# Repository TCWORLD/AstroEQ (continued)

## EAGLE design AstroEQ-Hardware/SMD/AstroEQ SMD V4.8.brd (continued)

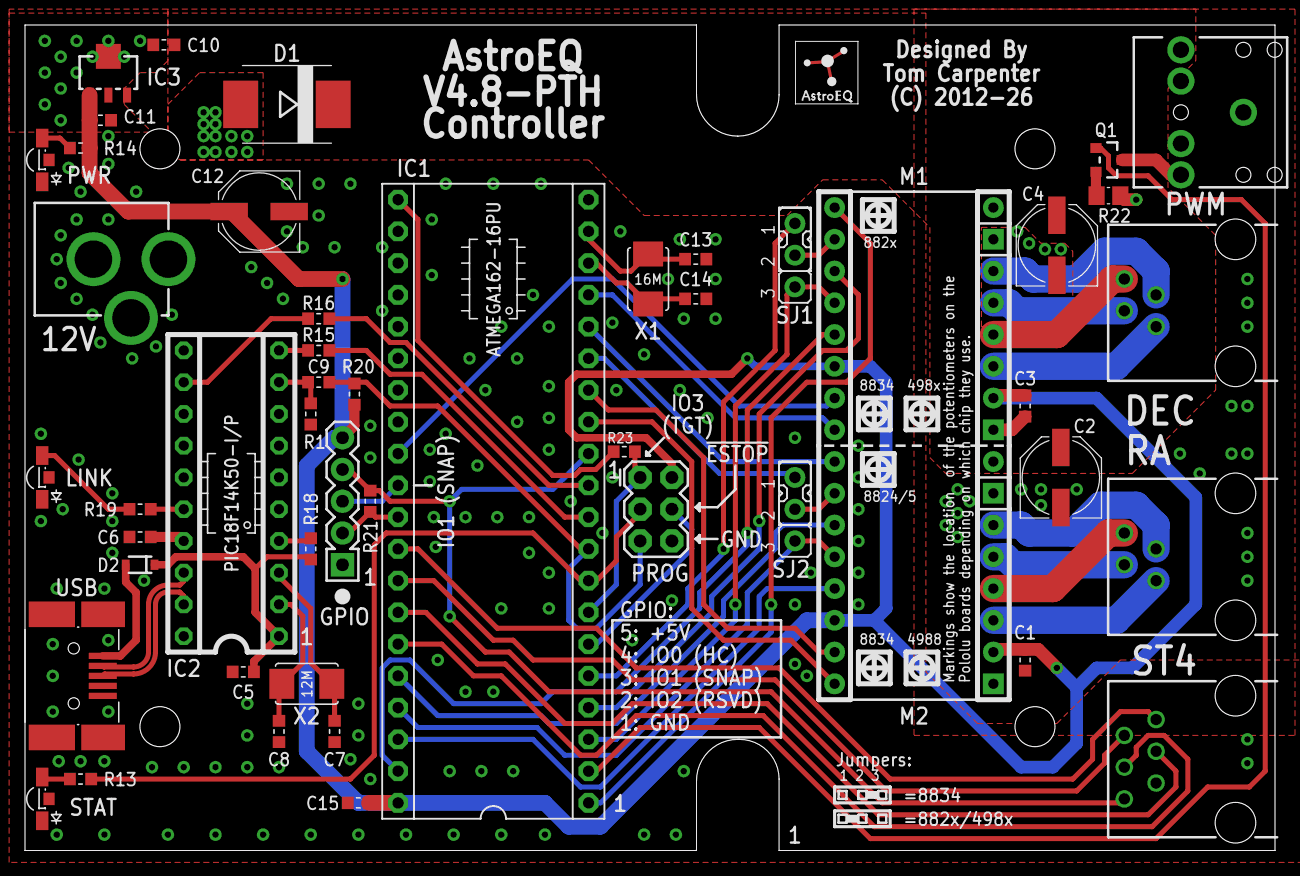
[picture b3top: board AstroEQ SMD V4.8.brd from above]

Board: 2 copper layers, 100.0 x 66.0 mm, 55 parts (0 on the bottom side), 62 nets.

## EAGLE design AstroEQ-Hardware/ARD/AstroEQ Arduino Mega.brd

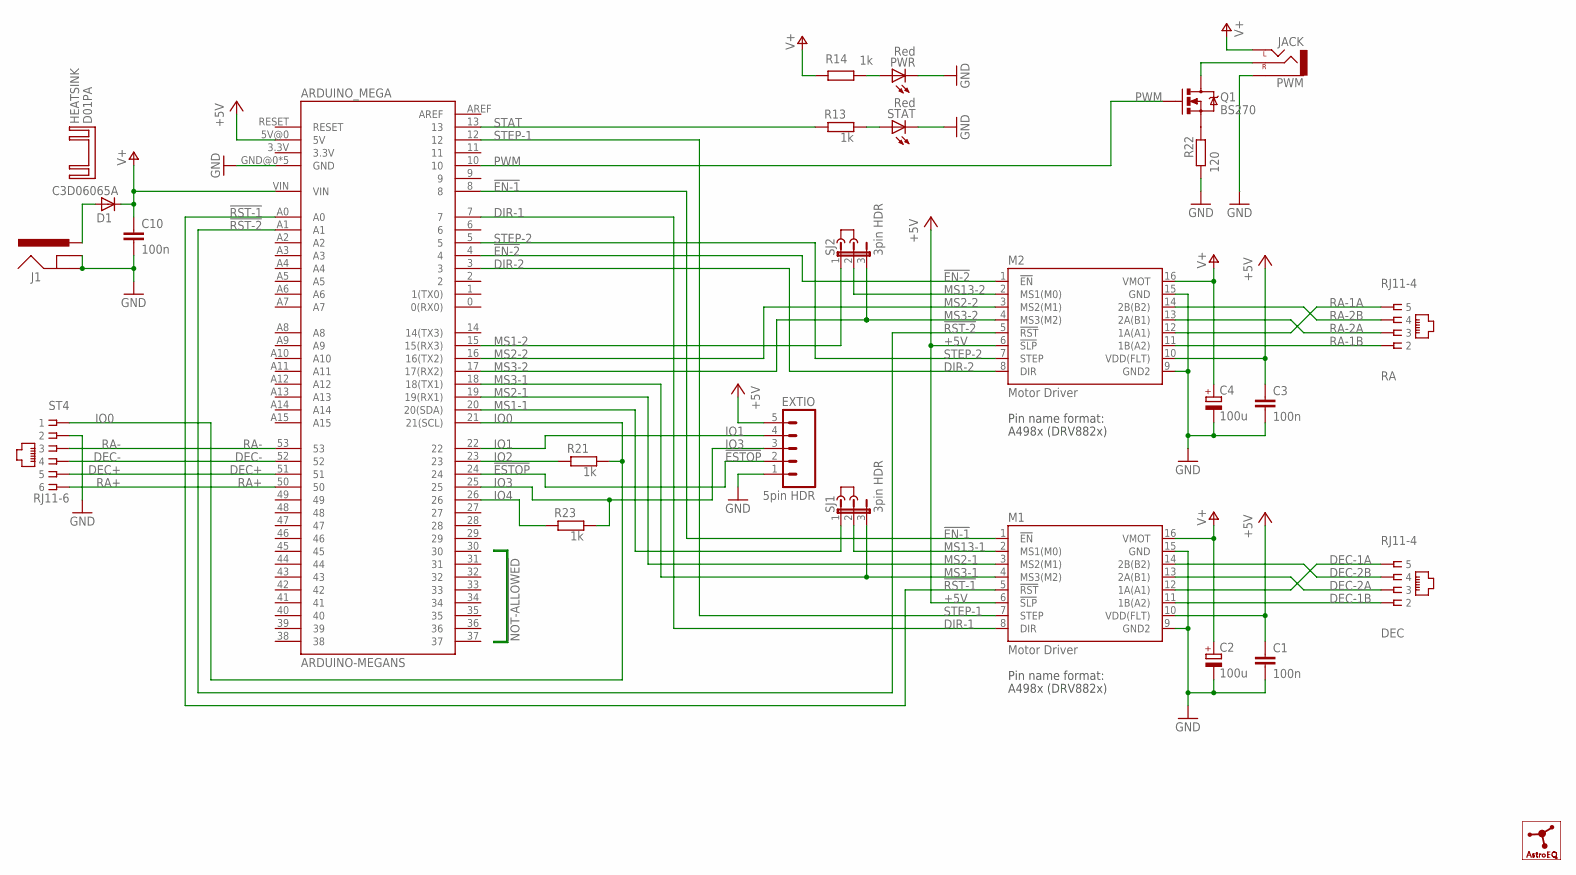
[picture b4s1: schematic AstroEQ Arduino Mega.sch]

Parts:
ARDUINO_MEGA: ARDUINO-MEGANS; ARDUINO_MEGA_NS
C1, C3, C10: 100n; C025-024X044; MPN SR205C104KAR
C2, C4: 100u; E2,5-7; MPN MCGPR25V107M6.3X11
D1: C3D06065A; TO220ACS; MPN C3D06065A
DEC: RJ11-4; RJ11-NO_SHIELD-4; MPN 95501-2641
EXTIO: 5pin HDR; 1X05
HEATSINK: D01PA
J1: POWER_JACKPTH; POWER_JACK_PTH; MPN MJ-179PH
J2, J3: DNI; JUMP; MPN 969102-0000-DA
LOGO1: ASTROEQ8MM; ASTROEQ
M1, M2: Motor Driver; DIP16-W; MPN CES-116-01-T-S
PWM: JACK; AUDIO-JACK-3.5MM-VERT
PWR: Red; LED3MM; MPN L-424HDT
Q1: BS270; TO-92; MPN BS270
R13: 1k; 0204/5; MPN MF12 1K
R14, R21, R23: 1k; 0204/7; MPN MF12 1K
R22: 120; 0204/7; MPN MF12 120R
RA: RJ11-4; RJ11-NO_SHIELD-4; MPN 95501-2641
SJ1, SJ2: 3pin HDR; JP2; MPN M20-9990345.
ST4: RJ11-6; RJ11-NO_SHIELD
STAT: Red; LED3MM; MPN L-424HDT

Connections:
!EN-1: ARDUINO_MEGA.8, M1.1 (!EN)
!EN-2: ARDUINO_MEGA.4, M2.1 (!EN)
!ESTOP: ARDUINO_MEGA.24, EXTIO.2
!RST-1: ARDUINO_MEGA.A0, M1.5 (!RST)
!RST-2: ARDUINO_MEGA.A1, M2.5 (!RST)
+5V: ARDUINO_MEGA.5V@0 (5V), C1.1, C3.1, EXTIO.5, M1.6 (!SLP), M1.10 (VDD(FLT)), M2.6 (!SLP), M2.10 (VDD(FLT))
DEC+: ARDUINO_MEGA.51, ST4.5
DEC-: ARDUINO_MEGA.52, ST4.4
DEC-1A: DEC.5, M1.12 (1A(A1))
DEC-1B: DEC.2, M1.11 (1B(A2))
DEC-2A: DEC.3, M1.13 (2A(B1))
DEC-2B: DEC.4, M1.14 (2B(B2))
DIR-1: ARDUINO_MEGA.7, M1.8 (DIR)
DIR-2: ARDUINO_MEGA.3, M2.8 (DIR)
GND: ARDUINO_MEGA.GND@0 (GND), ARDUINO_MEGA.GND@1 (GND), ARDUINO_MEGA.GND@2 (GND), ARDUINO_MEGA.GND@3 (GND), ARDUINO_MEGA.GND@4 (GND), C1.2, C2.-, C3.2, C4.-, C10.2, EXTIO.1, J1.GND, J1.GNDBREAK, M1.9 (GND2), M1.15 (GND), M2.9 (GND2), M2.15 (GND), PWM.1 (SLEEVE), PWR.K (C), R22.1, ST4.2, STAT.K (C)
IO0: ARDUINO_MEGA.21 (21(SCL)), R21.2, ST4.1
IO1: ARDUINO_MEGA.22, EXTIO.4
IO2: ARDUINO_MEGA.23, R21.1
IO3: ARDUINO_MEGA.25, EXTIO.3, R23.2
IO4: ARDUINO_MEGA.26, R23.1
MS1-1: ARDUINO_MEGA.20 (20(SDA)), SJ1.1
MS1-2: ARDUINO_MEGA.15 (15(RX3)), SJ2.1
MS2-1: ARDUINO_MEGA.19 (19(RX1)), M1.3 (MS2(M1))
MS2-2: ARDUINO_MEGA.16 (16(TX2)), M2.3 (MS2(M1))
MS3-1: ARDUINO_MEGA.18 (18(TX1)), M1.4 (MS3(M2)), SJ1.3
MS3-2: ARDUINO_MEGA.17 (17(RX2)), M2.4 (MS3(M2)), SJ2.3
MS13-1: M1.2 (MS1(M0)), SJ1.2
MS13-2: M2.2 (MS1(M0)), SJ2.2
PWM: ARDUINO_MEGA.10, Q1.2 (G)
PWM-ILIM: Q1.3 (S), R22.2
PWM-OUT: PWM.3 (RIGHT), Q1.1 (D)
PWRLED: PWR.A, R14.2
RA+: ARDUINO_MEGA.50, ST4.6
RA-: ARDUINO_MEGA.53, ST4.3
RA-1A: M2.12 (1A(A1)), RA.5
RA-1B: M2.11 (1B(A2)), RA.2
RA-2A: M2.13 (2A(B1)), RA.3
RA-2B: M2.14 (2B(B2)), RA.4
STAT: ARDUINO_MEGA.13, R13.1
STATLED: R13.2, STAT.A
STEP-1: ARDUINO_MEGA.12, M1.7 (STEP)
STEP-2: ARDUINO_MEGA.5, M2.7 (STEP)
V+: ARDUINO_MEGA.VIN, C2.+, C4.+, C10.1, D1.C, M1.16 (VMOT), M2.16 (VMOT), PWM.2 (LEFT), R14.1
VIN: D1.A, J1.PWR

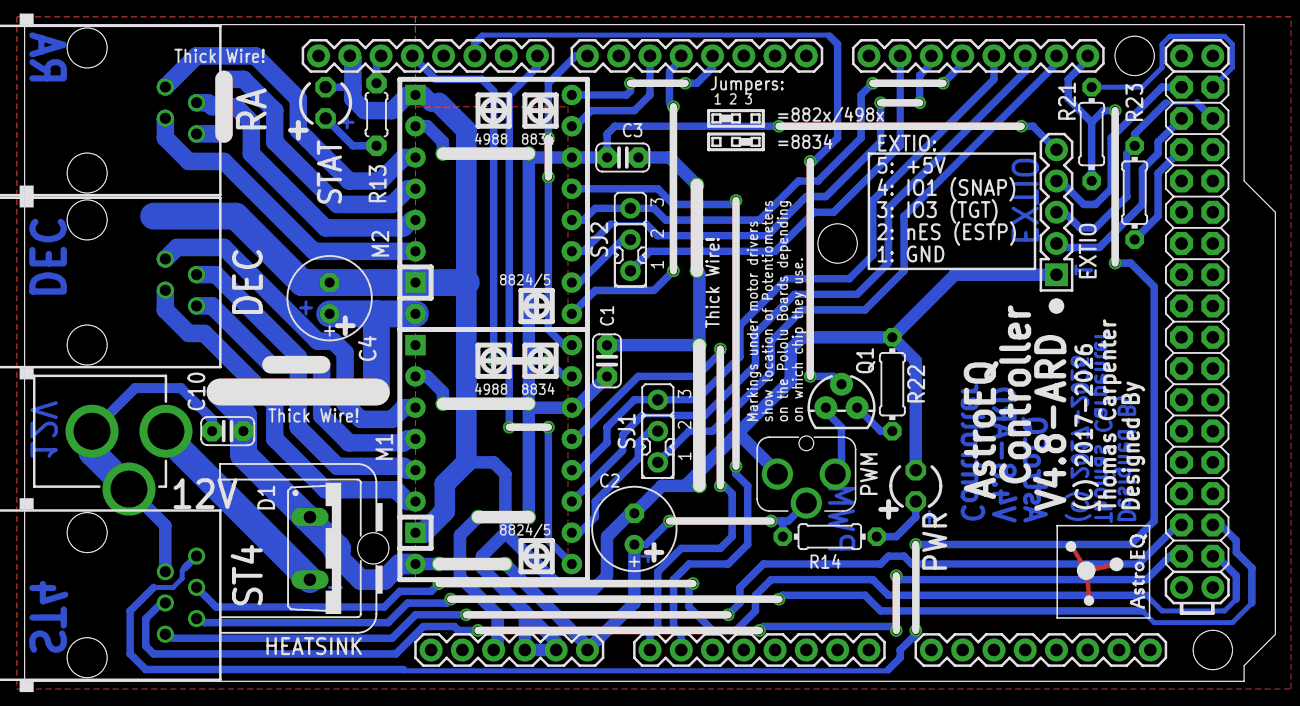
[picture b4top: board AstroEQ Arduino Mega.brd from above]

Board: 2 copper layers, 101.6 x 53.3 mm, 29 parts (0 on the bottom side), 44 nets.

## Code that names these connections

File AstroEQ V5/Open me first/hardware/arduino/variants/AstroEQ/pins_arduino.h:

/*
  pins_arduino.h - Pin definition functions for Arduino
  Part of Arduino - http://www.arduino.cc/

  Copyright (c) 2007 David A. Mellis

  This library is free software; you can redistribute it and/or
  modify it under the terms of the GNU Lesser General Public
  License as published by the Free Software Foundation; either
  version 2.1 of the License, or (at your option) any later version.

  This library is distributed in the hope that it will be useful,
  but WITHOUT ANY WARRANTY; without even the implied warranty of
  MERCHANTABILITY or FITNESS FOR A PARTICULAR PURPOSE.  See the GNU
  Lesser General Public License for more details.

  You should have received a copy of the GNU Lesser General
  Public License along with this library; if not, write to the
  Free Software Foundation, Inc., 59 Temple Place, Suite 330,
  Boston, MA  02111-1307  USA

  $Id: wiring.h 249 2007-02-03 16:52:51Z mellis $
*/

#ifndef Pins_Arduino_h
#define Pins_Arduino_h

#include <avr/pgmspace.h>

#define NUM_DIGITAL_PINS            35
#define NUM_ANALOG_INPUTS           0
#define analogInputToDigitalPin(p)  (-1)

#define digitalPinHasPWM(p)         ((p) == 5 || (p) == 6 || (p) == 8 || (p) == 9 || (p) == 10 || (p) == 30)

const static uint8_t SS   = 10;
const static uint8_t MOSI = 11;
const static uint8_t MISO = 12;
const static uint8_t SCK  = 13;

const static uint8_t LED_BUILTIN = 13;

#define digitalPinToPCICR(p)    ( (((p) >= 14) && ((p) <= 17)) || \
                                  (((p) >= 20) && ((p) <= 27)) || \
                                  (((p) >= 31) && ((p) <= 34)) ? (&PCICR) : ((uint8_t *)0) )
								  
#define digitalPinToPCICRbit(p) ( (((p) >= 20) && ((p) <= 27)) ? 0 : 1 )

#define digitalPinToPCMSK(p)    ( (((p) >= 20) && ((p) <= 27)) ? (&PCMSK0) : \
								  (((p) >= 14) && ((p) <= 17)) || \
                                  (((p) >= 31) && ((p) <= 34)) ? (&PCMSK1) : ((uint8_t *)0) )

#define digitalPinToPCMSKbit(p) ( (((p) >= 20) && ((p) <= 27)) ? ((p) - 20) : \
								  (((p) >= 14) && ((p) <= 17)) ? ((p) - 14) : ((p) - 27) )

#ifdef ARDUINO_MAIN

// On the Arduino board, digital pins are also used
// for the analog output (software PWM).

// ATMEL ATMEGA162 / ARDUINO
//
//                  +-\/-+
//  PWM(0)  (D 8) PB0  1|    |40  VCC
//  PWM(2)  (D 9) PB1  2|    |39  PA0 (D14)
//          (D19) PB2  3|    |38  PA1 (D15)
//          (D18) PB3  4|    |37  PA2 (D16)
// PWM(3B)  (D10) PB4  5|    |36  PA3 (D17)
//          (D11) PB5  6|    |35  PA4 (D31)
//          (D12) PB6  7|    |34  PA5 (D32)
//          (D13) PB7  8|    |33  PA6 (D33)
//                RST  9|    |32  PA7 (D34)
//          (D 0) PD0 10|    |31  PE0 (D28)
//          (D 1) PD1 11|    |30  PE1 (D29)
//          (D 2) PD2 12|    |29  PE2 (D30) PWM(1B)
//          (D 3) PD3 13|    |28  PC7 (D27)
// PWM(3A)  (D 5) PD4 14|    |27  PC6 (D26)
// PWM(1A)  (D 6) PD5 15|    |26  PC5 (D25)
//          (D 4) PD6 16|    |25  PC4 (D24)
//          (D 7) PD7 17|    |24  PC3 (D23)
//                XT2 18|    |23  PC2 (D22)
//                XT1 19|    |22  PC1 (D21)
//                GND 20|    |21  PC0 (D20)
//                      +----+
//


// these arrays map port names (e.g. port B) to the
// appropriate addresses for various functions (e.g. reading
// and writing)
const uint16_t PROGMEM port_to_mode_PGM[] = {
	NOT_A_PORT,
	(uint16_t) &DDRA,
	(uint16_t) &DDRB,
	(uint16_t) &DDRC,
	(uint16_t) &DDRD,
	(uint16_t) &DDRE,
};

const uint16_t PROGMEM port_to_output_PGM[] = {
	NOT_A_PORT,
	(uint16_t) &PORTA,
	(uint16_t) &PORTB,
	(uint16_t) &PORTC,
	(uint16_t) &PORTD,
	(uint16_t) &PORTE,
};

const uint16_t PROGMEM port_to_input_PGM[] = {
	NOT_A_PORT,
	(uint16_t) &PINA,
	(uint16_t) &PINB,
	(uint16_t) &PINC,
	(uint16_t) &PIND,
	(uint16_t) &PINE,
};

const uint8_t PROGMEM digital_pin_to_port_PGM[] = {
	PD, /* 0 */
	PD,
	PD,
	PD,
	PD,
	PD,
	PD,
	PD,
	PB, /* 8 */
	PB,
	PB,
	PB,
	PB,
	PB,
	PA, /* 14 */
	PA,
	PA,
	PA,
	PB, /* 18 */
	PB,
	PC, /* 20 */
	PC,
	PC,
	PC,
	PC,
	PC,
	PC,
	PC,
	PE, /* 28 */
	PE,
	PE,
	PA, /* 31 */
	PA,
	PA,
	PA,
};

const uint8_t PROGMEM digital_pin_to_bit_mask_PGM[] = {
	_BV(0), /* 0, port D */
	_BV(1),
	_BV(2),
	_BV(3),
	_BV(6),
	_BV(4),
	_BV(5),
	_BV(7),
	_BV(0), /* 8, port B */
	_BV(1),
	_BV(4),
	_BV(5),
	_BV(6),
	_BV(7),
	_BV(0), /* 14, port A */
	_BV(1),
	_BV(2),
	_BV(3),
	_BV(3), /* 18, port B */
	_BV(2),
	_BV(0), /* 20, port C */
	_BV(1),
	_BV(2),
	_BV(3),
	_BV(4),
	_BV(5),
	_BV(6),
	_BV(7),
	_BV(0), /* 28, port E */
	_BV(1),
	_BV(2),
	_BV(4), /* 31, port A */
	_BV(5),
	_BV(6),
	_BV(7),
};

const uint8_t PROGMEM digital_pin_to_timer_PGM[] = {
	NOT_ON_TIMER, /* 0 - port D */
	NOT_ON_TIMER,
	NOT_ON_TIMER,
	NOT_ON_TIMER,
	NOT_ON_TIMER,
	TIMER3A,
	TIMER1A,
	NOT_ON_TIMER,
	TIMER0A, /* 8 - port B */
	TIMER2A,
	TIMER3B,
	NOT_ON_TIMER,
	NOT_ON_TIMER,
	NOT_ON_TIMER,
	NOT_ON_TIMER,/* 14, port A */
	NOT_ON_TIMER,
	NOT_ON_TIMER,
	NOT_ON_TIMER,
	NOT_ON_TIMER, /* 18, port B */
	NOT_ON_TIMER,
	NOT_ON_TIMER, /* 20, port C */
	NOT_ON_TIMER,
	NOT_ON_TIMER,
	NOT_ON_TIMER,
	NOT_ON_TIMER,
	NOT_ON_TIMER,
	NOT_ON_TIMER,
	NOT_ON_TIMER,
	NOT_ON_TIMER, /* 28, port E */
	NOT_ON_TIMER,
	TIMER1B,
	NOT_ON_TIMER, /* 31, port A */
	NOT_ON_TIMER,
	NOT_ON_TIMER,
	NOT_ON_TIMER,
};

#endif

#endif

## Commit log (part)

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2012-02-29 Initial commit of project. Currently tracking is at incorrect speed, I'm working on it :S
2012-04-22 Further Information
2012-04-23 Fixed bug with motor control with user chosen bValues.
2012-07-01 Wiki files
2012-12-19 Added Downloads Folder
2013-01-21 Added SMD design to fit inside EQ5 mount shell.
2013-05-28 Added AstroEQ Configuration Utility
    Added utility for configuring AstroEQ6 Firmware.
2013-06-22 Added AstroEQ Kit assembly pictures
2013-07-06 Added ST4 Modification Photos
    This simple mod gives AstroEQ full support for ST4 guiding. The latest
    firmware revision is required.
2013-08-10 Added Bootloader for Atmega162
    The bootloader is required if you are making your own AstroEQ board
    using the ATMega162. If you have bought a kit or ready assembled board
    from me, this is not needed.
2013-09-30 AstroEQ 6.3 Release (critical)
    6.3 fixes a glitch which causes the mount to not decelerate under EQMOD
    Rate Limiting. Everyone is advised to update to this version.
2013-10-13 Added Linux version of AstroEQ Configuration Utility
    For those using Linux (Ubuntu or Debian), you can now use the
    configuration utility. EQMOD can be successfully run under WINE allowing
    Linux users to take advantage of AstroEQ. However AstroEQ Configuration
    could not. Now there is a native Linux version of the config utility.
2013-12-14 Added apt repository for Linux
    Linux users can now install astroequploader through apt-get. Add the
    following to your /etc/apt/sources.list:
    deb https://github.com/TCWORLD/AstroEQ/raw/master/repo stable main
2014-01-12 AstroEQ Software V6.8 and Hardware V4.3
    S-V6.8: Faster processing of Serial commands for better guiding
    responsiveness. You can use the config utility to fetch the new
    firmware.
    H-V4.3: Minor PCB rearrangement to make soldering and assembly easier.
    Nothing changed electrically.
2014-06-04 AstroEQ7 Major Release
    Please see http://www.astroeq.co.uk/downloads for release notes.
2014-06-06 Final corrections to apt repository.
    Linux users can download the config utility by adding to the apt
    sources.list:
    https://github.com/TCWORLD/AstroEQ/raw/master/repo stable main
2014-06-23 Fixes #14 Upload Issues for Mega2560
    There was a glitch in the configuration utility which meant it failed to
    upload firmware for the Arduino Mega2560 and Mega1280 boards. This is
    fixed.
2015-03-01 Update DIY Eagle Designs
    (1) Bring AstroEQ-DIY up to date (V4.4)
    (2) Export AstroEQ-DIY schematic to PDF
    (3) Make sure the etch file doesn't have holes in pads
    (4) Add AstroEQ-ARD variant - Arduino Mega sheild
2015-05-07 Correct Board-Schematic Inconsistencies
    In the SMD design, the board and schematic files in Eagle had become
    inconsistent. This has been corrected.
2015-06-08 Update PCB Logo
    Add AstroEQ logo to PCB hardware designs.
2016-02-01 Add support for changing serial port number
    Support has been added to the SerialLink code to allow the Arduino Mega
    to be used with a different serial port in case an external USB-Serial
    is to be used or something like Bluetooth. Simply change the #define
    SERIALn 0 line in the SerialLink.h file.
2016-02-01 Update PinMappings
    Update the pin mappings to firstly tidy up the file to make things
    clearer, and secondly to add definitions for the GPIO pins.
2016-02-02 Correct Standalone Mode Initialisation
    Update the standalone mode initialisation code to enable sidereal
    tracking and hopefully allow everything to work correctly.
2016-02-21 Fix ST4 Pin Direction (URGENT!)
    The ST4 pin directions were misakenly set to be as outputs when updating
    the firmware for the v7.5 developments. This has been corrected. If you
    are using a version without this fix, make sure to apply it before using
    the ST4 port!
2017-02-12 Update Firmware Download
    Update the downloads folder with latest firmware.
2017-02-17 Delete Upgrade paths from 6.x
    Given that it was 3 years ago when I jumpt to version 7.x I don't think
    there is any need now for references back to the archaic version.
2017-04-09 Update Hardware Designs
    Minor corrections to part attributes and some components in the V4.7
    design moved slightly to avoid collisions as found during the prototype
    build.
2017-04-09 Update README and Downloads
    1. Update the downloads folder with the latest firmware/config utilty
    2. Update README to bump version number and add note about Windows 10
    and the AstroEQ driver.
2017-04-18 Fix ST4 Routines
    The new ST4 routines were preventing EQMOD from slewing North.
    Additionally detection of the basic handcontroller speeds was a little
    buggy. This has been fixed.
2017-04-18 Update Readme Current Release Version to V8.0
    Update the version numbers in the readme to match new release.
2017-06-26 New AstroEQ Firmware Release
    New firmware release after porting to C.
2017-06-26 Add AstroEQ Config Utility Processing 3 Project
    Add source code for the AstroEQ configuration utility.
2017-07-02 Bump Version Numbers in README
2017-07-16 Make AstroEQ.h Load Version Number from VerNum.txt
    VerNum.txt is a text file in the AstroEQ Atmel Studio project which
    contains the current version number. This value is used by build event
    scripts to update the firmware version in the config utility version
    records.
    Using a bit of clever preprocessor trickery, the VerNum.txt file is
    loaded in to the code at compile time and converted into an inline
2017-07-18 Fix Header Text
    In the AstroEQ.h file refer people to VerNum.txt to get current version
    number.
2017-07-19 Update Linux Config Utility to Latest Version
    Update the Linux version of the configuration utility to the latest
    version (3.7.2).
2017-09-02 Update Windows Config Utility to Bump Version Number
    The version number bumped as a result of corrections to the handling of
    AVRdude under Linux.
2017-10-15 Add DPInst to Driver Package
    Add microsoft driver installer to make installing the AstroEQ driver
    easier.
2017-10-16 Change Configuration Structure (CRC + Vernum)
    NOTE: Changes require new config utility. Will follow.
    Change the header for the configuration structure. The new header uses a
    shortened ID string (AEQ rather than AstroEQ). The freed bytes now
    contain a version number string and a CRC8-CITT word.
    The CRC and version number will aid in future changes to the
    configuration structure.
2017-10-19 Improve Readability of Motion Mode
    Use functions when checking if the motion is slew/goto or
    highspeed/lowspeed. This just improves readability.
2018-02-03 Remove Need for Temporary Directory
    Remove the need for a temp directory for the config utility. Finally
    figured out how to get AVRDude to cope with spaces in the config file
    path.
2018-02-03 Release Latest Firmware
    Release the latest firmware and configuration utility.
    Firmware V8.11
    Config V3.8.2
2018-02-19 Update Config Utility
    Update Linux and Windows config utility downloads to latest version.
2018-06-02 Update Atmel Studio Post-Build Step
    Update the post-build step to match the new versions.txt structure.
2018-06-02 Compile New Config Utility Version
    Compile new version of the configuration utility.
2018-06-23 Improve :O2x Handling
    The purpose of EQMOD using the :Oxx command has become clearer. This is used to control up to two GPIO pins, for example to trigger a camera shutter.
    The :O1x command in AstroEQ is used to enter programming mode, so in order to tell EQMOD not to use the SNAP1 interface, AstroEQ now reports an error packet when :O1x is issued in run-mode. The confi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
    This should provide a secure way of fixing issue #24.
    AstroEQ V4.6 and newer, as well as Mega variants, have a spare GPIO pin not used for standalone mode. To still allow a feature
2018-06-23 Compile Release Version of Firmware
    Compile Release Version of Firmware V8.12 and Configuration Utility V3.9.0.
    This Fixes Issue #24.
2018-09-01 Fix typos
2018-09-01 Compile AstroEQ Release Firmware
    Compile release version of AstroEQ firmware.
    Also update README.
2018-09-02 Change default value for GVal to lowspeed slew mode
2019-01-08 Compile AstroEQ Firmware
    This is a minor change which only affects the MKS Gen L and RAMPS 1.4 variants.
2019-02-26 Optimise Synta Response
    Optimisation to response code.
2019-03-13 Add Emergency Stop Input
    Add handling code for an e-stop input that when pulled low will cause the mount to stop moving and prevent further movements until released.
    On the ATMega162 based AstroEQ devices, this will be the MISO pin on the ISP header.
2019-12-16 AstroEQ Firmware V8.17 Release
    Compile firmware release and new config utility version.
2020-01-18 Release New Config Utility Version 3.9.2
    A mistake in the config utility resulted in several parameters not being uploaded to the AstroEQ.
    This fixes #29
2020-06-09 Add Commenting to RAMPS Pinout
    Add some additional commenting as to which pins on the Ramps board are used.
2021-01-08 Bump Version Number
2022-04-13 Update AstroEQ6.cproj
    Fixed path for latest Atmel Studio
2022-09-23 Package V8.20 firmware in config utility
    When the new firmware was released, the download version of the config utility was not updated to include it.
2022-12-11 Add :q command handling for Run Mode
    No idea if this is correct, the protocol documentation is hellishly unclear.
2022-12-11 Package New Firmware Hex into Config Utility Download
2024-02-04 Add :P Command Handling
    This allows setting the auto-guiding rate via the Synta protocol. There are 5 rates defined - 1x, 0.75x, 0.5x, 0.25x, and 0.125x.
    I don't know if EQMOD supports this command, but might as well add the implementation in case it does or later decides to.
2024-09-01 Correct Conversion to Enum for MotorRunning
    Accidentally inverted the meaning of Stopped/Running.
2026-01-22 Ensure :J is not treated as an unknown command in run mode
    The new error reporting accidentally made :J and unknown command preventing mount operations from being performed.
2026-01-22 Add Lunar/Solar ST4 Mode Options
    When selected, these scale the sidereal IVal to approximate the equivalent Lunar or Solar IVal to within a reasonable margin of error and use the calculated value as the base speed for ST4 movements.
